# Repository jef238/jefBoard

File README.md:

# jefBoard

## Cos'è

JefBoard è una scheda di sviluppo basata sul microcontroller Attiny2313 della ATMEL. Si presta allo sviluppo di applicazioni di varia natura e integra la predisposizione per la scheda WiFI ESP-01 (Opzionale) e il connettore per la programmazione ISP dell'Attiny2313.
Alcune caratteristiche:
- JefBoard espone tutti i pin dell'Attiny2313 per il loro utilizzo.
- JefBoard permette la realizzazione di applicazioni con supporto WiFi (il modulo ESP-01 comunica tramite connessione seriale con l'Attiny2313).
- JefBoard può essere assemblata anche senza l'ESP-01 e relativi componenti di alimentazione se non si necessita di supporto WiFi abbassando ulteriormente il costo.
- JefBoard è una scheda di piccole dimensioni 6x4 cm.

## Attiny 2313 pinout

# Schema ed elenco componenti

# PCB Layout
Per reperire la PCB scrivi al mio indirizzo giuseppe.culotta@gmail.com

## Elenco componenti

| Sigla | Valore                        | Tipo			        | Note                                        |
|-------|-------------------------------|-------------------------------|---------------------------------------------|
| C1    | 100n           		| Condensatore poliestere        |				              |    
| C2    | 100u           		| Condensatore elettrolitico     |					      |
| C4    | 10u            		| Condensatore elettrolitico     | (Opzionale - Solo in caso di supporto WIFI) |	
| C5    | 22p            		| Condensatore ceramico          |					      |
| C6    | 22p            		| Condensatore ceramico          | 					      |
| ESP01 |                 		| Connettore pin		| (Opzionale - Solo in caso di supporto WIFI) |
| IC1   | ATtiny2313/ATtiny2313a        | AVR			        |				              |
| IC2   | LM1117DTX 3.3V 		|			        | (Opzionale - Solo in caso di supporto WIFI) |	
| JP1   |                  		| Connettore tipo M100.1	| (Opzionale)                  		      |
| JP2   |                  		| Connettore tipo M100.1	| (Opzionale)                                 |
| LED1  |                  		| LED3MM                        |				              |
| PWR   |                  		| Connettore tipo W237-102      | (Opzionale)                                 |
| Q1    |                   		| Quarzo 4MHZ    	        |	                                      |
| R1    | 10k            		| 1/4w		                |                                             |
| R2    | 1k            		| 1/4w 				| (Opzionale - Solo in caso di supporto WIFI) |	
| R3    | 2k            		| 1/4w 	        		| (Opzionale - Solo in caso di supporto WIFI) |	
| R4    | 220            		| 1/4w                		| 					      |
| RESET1|                  		| Microswitch                   |                                             |
| RESET2|                 		| Microswitch			| (Opzionale - Solo in caso di supporto WIFI) |
| SV2   |                   		| Connettore pin                |                                             |
         
# Programmazione

Io utilizzo Xcode e [CrossPack for AVR Development](https://github.com/obdev/CrossPack-AVR) in ambiente Mac.

In ambiente Windows vi consiglio di utilizzare Atmel Studio 7 ma sembra che recentemente sia stato sostituito da un altro prodotto: https://www.microchip.com/en-us/tools-resources/develop/microchip-studio.
Se utilizzate Atmel Studio ricordate di selezionare l'Attiny2313a come chip durante la creazione del progetto ed eseguire i seguenti step:
- Project->Properties->Toolchain->AVR/GNU C Compiler->Symbols: aggiungere F_CPU=2000000  (In questo caso la frequenza di clock è di 2MHZ)

- Impostare USBTINY come external tool (https://www.programming-electronics-diy.xyz/2020/09/using-usbtinyisp-programmer-with-atmel.html), in questo modo potete scrivere il firmware in formato hex sul chip direttamente dall'interfaccia di Atmel Studio dal menu Tools.

Come programmatore hardware per l'ISP ho utilizzato l'USBtinyISP:

## 1. Impostazione FUSE bits

Questa procedura deve essere eseguita solo una volta poichè serve a settare le impostazioni di base del bootloader del chip   

- Utilizzare AVR Calculator per ottenere la stringa corretta (http://www.engbedded.com/fusecalc)

    ESEMPI:
    ```
    /* Oscillatore interno 1MHZ */     						-U lfuse:w:0x64:m -U hfuse:w:0xdf:m -U efuse:w:0xff:m
    /* Quarzo esterno da 3 a 8MHZ */   						-U lfuse:w:0xfd:m -U hfuse:w:0xdf:m -U efuse:w:0xff:m
    /* Quarzo esterno da 16MHZ con CKDIV8 e frequenza effettiva 2MHZ */		-U lfuse:w:0x5e:m -U hfuse:w:0xdf:m -U efuse:w:0xff:m     
    ```
- Impostare i FUSE Bits nell'Attiny2313:
   ```
   avrdude -c usbtiny -p t2313 -e -U lfuse:w:0xfd:m -U hfuse:w:0xdf:m -U efuse:w:0xff:m
   ```

## 2a. Compilazione su Xcode (Mac)

- Modificare le righe seguenti nel file Makefile (ATTENZIONE: la riga FUSES deve essere identica alle impostazioni di FUSE Bits dell'Attiny2313; in questo esempio si utilizza un quarzo esterno da 4MHZ):
	```
	DEVICE     = attiny2313
	CLOCK      = 4000000
	PROGRAMMER = -c usbtiny -p attiny2313
	OBJECTS    = main.o
	FUSES      = -U lfuse:w:0xFD:m -U hfuse:w:0xDF:m -U efuse:w:0xFF:m -U lock:w:0xFF:m
  ```
- effettuare build (verrà generato main.hex)

## 2b. Compilazione su Atmel Studio (Windows)

- Menu Build->Build "nome progetto"
                                                             
## 3. Collegare l'USBtinyISP

- Assicurarsi di aver correttamente collegato il programmatore al computer e di aver installato i driver per il suo funzionamento (su Mac non è necessario installare driver)

- Collegare l'USBtinyISP al connettore SV2

## 4a. Flash su Mac

- Caricare il file .hex nel chip: 
   ```
   avrdude -c usbtiny -p t2313 -e -U flash:w:main.hex
   ```
## 4b. Flash su Windows (Atmel Studio)

- Menu Tools->USBTiny (per la configurazione vedi https://www.programming-electronics-diy.xyz/2020/09/using-usbtinyisp-programmer-with-atmel.html)

# Utilizzo dell'ESP01 per il supporto WIFI

L'ESP01 è un modulo SOC basato sul chip ESP8266 che permette di aggiungere il supporto al WIFI in modo semplice ed economico.
Prima di inserirlo sulla jefBoard è necessario fare una precisazione:
L'ESP01 viene fornito generalmente con un firmware dotato di soli comandi AT per cui prima di utilizzarlo nei nostri progetti è necessario caricare il firmware nodeMCU (https://it.wikipedia.org/wiki/NodeMCU). Con questo firmware è possibile programmare facilmente l'ESP01 tramite linguaggio LUA ed è possibile compilare una versione custom di nodeMCU con il supporto delle librerie/funzionalità necessarie in base all'utilizzo su https://nodemcu-build.com.

E' necessario inoltre dotarsi di un adattore USB seriale TTL:

## Istruzioni per l’installazione di esptool su MACOSX:

- Scaricare e scompattare esptool (https://github.com/espressif/esptool)

- Assicurarsi di avere Python 1.7 o successivo installato sul sistema

- Spostarsi sulla directory appena scompattata ed eseguire:
   ```
   sudo python setup.py install
   ```

## Istruzioni per flash nodemcu su ESP01
Esistono tanti modi per abilitare la modalità flash su ESP-01 (una ricerca su google è altamente consigliata...). Tempo fa ho realizzato una scheda che per comodità mi permette di riavviare tramite reset l'ESP01 (pulsante 1) mentre metto a massa il pin GPIO0 (pulsante 2):

- Posizionare l’ESP01 e l’interfaccia seriale/USB sulla scheda di programmazione:

- Per settare l’ESP01 in modalità flash tenere premuto il pulsante 2 e contemporaneamente effettuare un reset premendo e rilasciando il pulsante 1; dopo qualche istante rilasciare il pulsante 2.

- Effettuare il comando (nodemcu_base_int.bin è il nome del file del firmware nodemcu da flashare vedi cartella esp8266):
   ```  
   python esptool.py --port /dev/tty.wchusbserialfa140 write_flash 0x00000 nodemcu_base_int.bin
   ```
- (opzionale) restore firmware originale (11/12/2019)
   ``` 
   python esptool.py --port /dev/tty.wchusbserialfd130 write_flash 0x00000 v0.9.2.2\ AT\ Firmware.bin
   ``` 
## Programmazione ESP01 tramite script LUA
Una volta caricato il firmware nodeMCU è possibile caricare gli script LUA. Il file denominato init.lua viene caricato all'avvio in maniera automatica.
E' possibile utilizzare il software ESPlorer (https://github.com/4refr0nt/ESPlorer) sia per caricare sia gli script LUA che per gestire al meglio l'ESP01.

# Utilizzo di jefBoard come server WIFI
In questo caso l'ESP01 funge da server in ascolto sulla porta 8080 tramite connessione WIFI; Ricevuto il comando lo inoltra tramite la connessione seriale verso l'Attiny2313.
Per questo utilizzo è necessario che la scheda sia equipaggiata con l'ESP01 aggiornata con il firmware nodeMCU, ed i relativi componenti. Di seguito un esempio di file init.lua (da caricare sull'ESP01) e del codice da utilizzare sull'Attiny2313:

## init.lua (ESP01)

```
wifi.setmode(wifi.SOFTAP)
cfg={}
cfg.ssid="jefBoard"
wifi.ap.config(cfg)

uart.setup(0, 9600, 8, uart.PARITY_NONE, uart.STOPBITS_1, 1)

sv = net.createServer(net.TCP, 30)

function receiver(sck, data)
  print(data)  --senda data to jefBoard by serial
end

if sv then
  sv:listen(8080, function(conn)
    conn:on("receive", receiver)    
  end)
end
```

## main.c (jefBoard/Attiny2313)

```
#define F_CPU 4000000 UL // 4 MHz Crystal

#include <avr/io.h>
#include <util/delay.h>
#include <avr/interrupt.h>

// Define baud rate
#define USART_BAUDRATE 9600
#define BAUD_PRESCALE (((F_CPU / (USART_BAUDRATE * 16UL))) - 1)

volatile unsigned char value;
/* This variable is volatile so both main and RX interrupt can use it.
 It could also be a uint8_t type */

/* Interrupt Service Routine for Receive Complete
 NOTE: vector name changes with different AVRs see AVRStudio -
 Help - AVR-Libc reference - Library Reference - <avr/interrupt.h>: Interrupts
 for vector names other than USART_RX_vect for Attiny2313 */

void dosomething(); //Exec something

void USART_Init(void) {
  // Set baud rate
  UBRRL = BAUD_PRESCALE; // Load lower 8-bits into the low byte of the UBRR register
  UBRRH = (BAUD_PRESCALE >> 8);
  /* Load upper 8-bits into the high byte of the UBRR register
   Default frame format is 8 data bits, no parity, 1 stop bit
   to change use UCSRC, see AVR datasheet*/

  // Enable receiver and transmitter and receive complete interrupt
  UCSRB = ((1 << TXEN) | (1 << RXEN) | (1 << RXCIE));
}

void USART_SendByte(uint8_t u8Data) {

  // Wait until last byte has been transmitted
  while ((UCSRA & (1 << UDRE)) == 0);

  // Transmit data
  UDR = u8Data;
}

// not being used but here for completeness
// Wait until a byte has been received and return received data
uint8_t USART_ReceiveByte() {
  while ((UCSRA & (1 << RXC)) == 0);
  return UDR;
}

ISR(USART_RX_vect) {
  if (UDR != 0x0A) value = UDR; //read UART register into value except <RETURN> key
}

void dosomething() {
  //Exec something    
}

int main(void) {

  USART_Init(); // Initialise USART
  sei(); // enable all interrupts

  //If received data from serial match 'd' char exec dosomething() function
  while (1) {
    if (value == 0x64) dosomething(); //ASCII for 'd'     
  }

  return 0;
}
``` 
## Contatti

giuseppe.culotta@gmail.com

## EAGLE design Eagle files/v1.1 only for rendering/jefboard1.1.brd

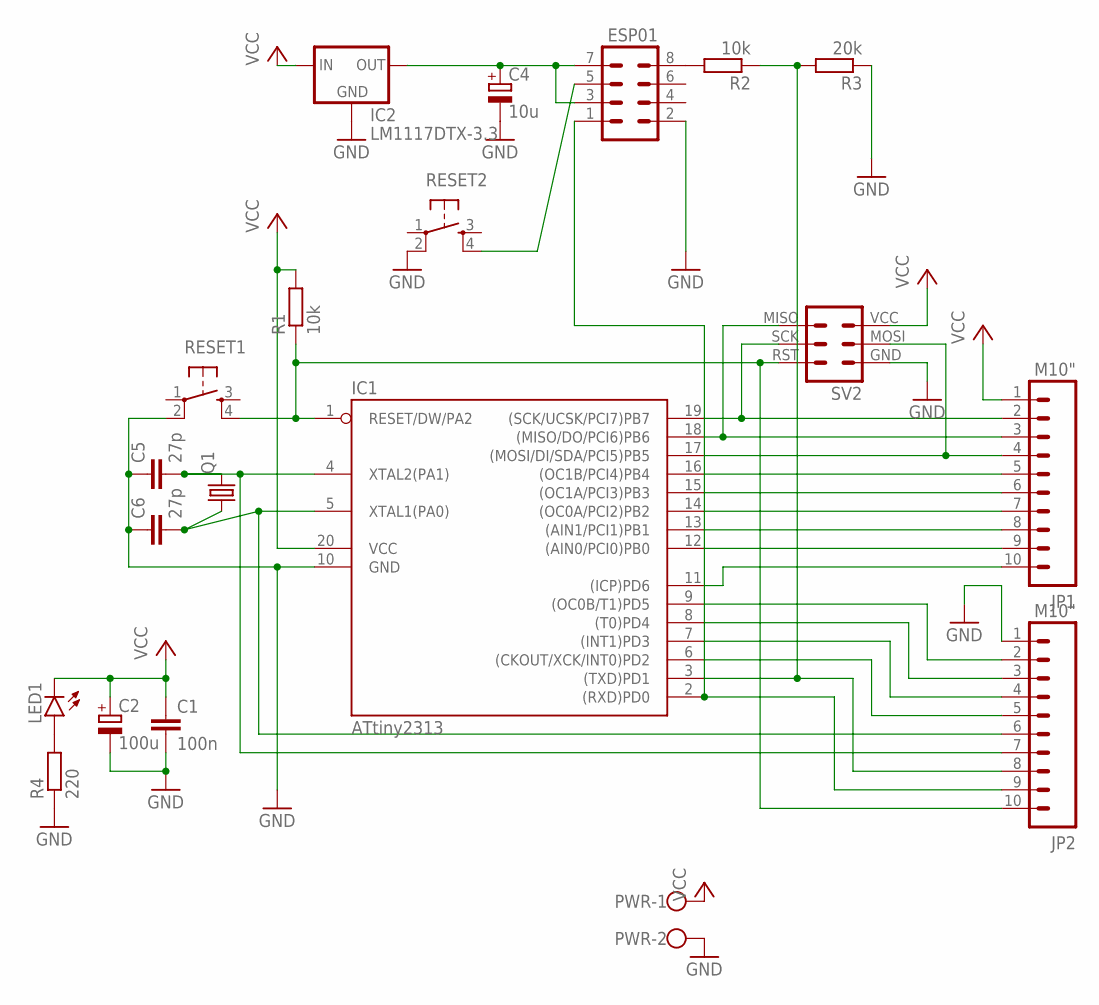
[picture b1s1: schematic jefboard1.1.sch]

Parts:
C1: 100n; C025-025X050
C2: 100u; E2,5-5
C4: 10u; E2,5-5
C5, C6: 27p; C2.5-2
ESP01: MA04-2
IC1: ATtiny2313; DIL20
IC2: LM1117DTX-3.3; TO252
JP1, JP2: M10"; 1X10
LED1: LED3MM
PWR: W237-102
Q1: CRYSTALHC49S; HC49/S
R1, R2: 10k; 0207/5V
R3: 20k; 0207/5V
R4: 220; 0207/5V
RESET1, RESET2: TAC_SWITCHPTH; TACTILE-PTH
SV2: MA03-2

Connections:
GND: C1.2, C2.-, C4.-, C5.1, C6.1, ESP01.2, IC1.10 (GND), IC2.1 (GND), JP2.1, PWR.2, R3.1, R4.1, RESET1.2, RESET2.2, SV2.GND
unnamed: C4.+, ESP01.3, ESP01.7, IC2.TAB (OUT)
unnamed: C5.2, IC1.4 (XTAL2(PA1)), JP2.7, Q1.2
unnamed: C6.2, IC1.5 (XTAL1(PA0)), JP2.6, Q1.1
unnamed: IC1.1 (RESET/DW/PA2), JP2.10, R1.1, RESET1.4, SV2.RST
unnamed: IC1.19 ((SCK/UCSK/PCI7)PB7), JP1.2, SV2.SCK
unnamed: IC1.18 ((MISO/DO/PCI6)PB6), JP1.3, SV2.MISO
unnamed: IC1.17 ((MOSI/DI/SDA/PCI5)PB5), JP1.4, SV2.MOSI
unnamed: IC1.16 ((OC1B/PCI4)PB4), JP1.5
unnamed: IC1.15 ((OC1A/PCI3)PB3), JP1.6
unnamed: IC1.14 ((OC0A/PCI2)PB2), JP1.7
unnamed: IC1.13 ((AIN1/PCI1)PB1), JP1.8
unnamed: IC1.12 ((AIN0/PCI0)PB0), JP1.9
unnamed: IC1.11 ((ICP)PD6), JP1.10
unnamed: IC1.9 ((OC0B/T1)PD5), JP2.2
unnamed: IC1.8 ((T0)PD4), JP2.3
unnamed: IC1.7 ((INT1)PD3), JP2.4
unnamed: IC1.6 ((CKOUT/XCK/INT0)PD2), JP2.5
unnamed: IC1.3 ((TXD)PD1), JP2.8, R2.1, R3.2
unnamed: ESP01.5, RESET2.4
unnamed: ESP01.8, R2.2
unnamed: LED1.A, R4.2
RX: ESP01.1, IC1.2 ((RXD)PD0), JP2.9
VCC: C1.1, C2.+, IC1.20 (VCC), IC2.2 (IN), JP1.1, LED1.K (C), PWR.1, R1.2, SV2.VCC

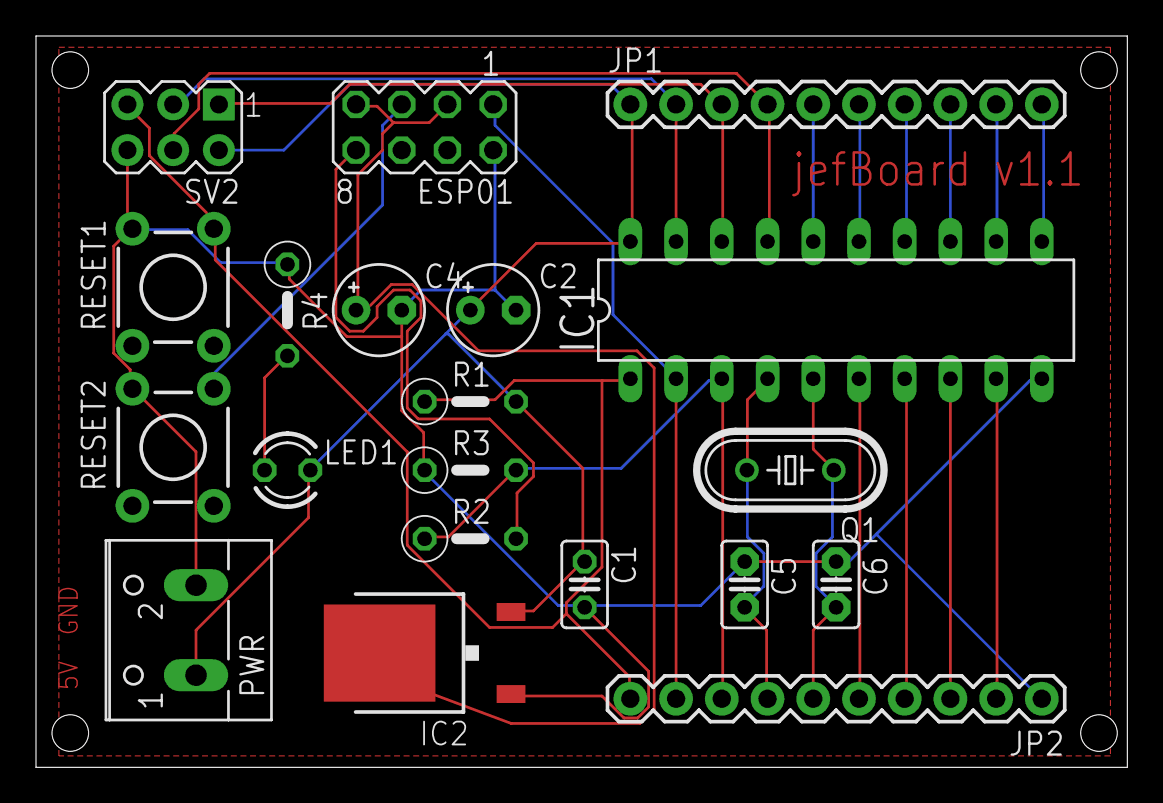
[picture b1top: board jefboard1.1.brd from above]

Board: 2 copper layers, 60.6 x 40.6 mm, 20 parts (0 on the bottom side), 24 nets.

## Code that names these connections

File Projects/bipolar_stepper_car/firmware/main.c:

/* Name: main.c
 * Author: <insert your name here>
 * Copyright: <insert your copyright message here>
 * License: <insert your license reference here>
 */

#include <avr/io.h>
#include <util/delay.h>

void myDelay();
void up();
void down();
void left();
void right();

int main(void)
{
    
    DDRB |= (1 << PB6) | (1 << PB5) | (1 << PB4) | (1 << PB3) | (1 << PB2) | (1 << PB1) | (1 << PB0); //Setup as output
    DDRD |= 1 << PD6; //Setup as output
    
    DDRD &= ~(1 << PD5); //Setup as input
    PORTD |= (1 << PD5); //Enable pullup resistor
    
    DDRD &= ~(1 << PD4); //Setup as input
    PORTD |= (1 << PD4); //Enable pullup resistor
    
    DDRD &= ~(1 << PD3); //Setup as input
    PORTD |= (1 << PD3); //Enable pullup resistor
    
    DDRD &= ~(1 << PD2); //Setup as input
    PORTD |= (1 << PD2); //Enable pullup resistor
    
#define Ax_on  PORTB |= (1 <<  PB2);
#define Bx_on  PORTB |= (1 <<  PB1);
#define Cx_on  PORTB |= (1 <<  PB0);
#define Dx_on  PORTD |= (1 <<  PD6);
#define Ax_off  PORTB &= ~(1 <<  PB2);
#define Bx_off  PORTB &= ~(1 <<  PB1);
#define Cx_off  PORTB &= ~(1 <<  PB0);
#define Dx_off  PORTD &= ~(1 <<  PD6);

#define Ay_on  PORTB |= (1 <<  PB6);
#define By_on  PORTB |= (1 <<  PB5);
#define Cy_on  PORTB |= (1 <<  PB4);
#define Dy_on  PORTB |= (1 <<  PB3);
#define Ay_off  PORTB &= ~(1 <<  PB6);
#define By_off  PORTB &= ~(1 <<  PB5);
#define Cy_off  PORTB &= ~(1 <<  PB4);
#define Dy_off  PORTB &= ~(1 <<  PB3);
    
    while(1){
        if ((PIND & (1 << PD5)) == 0) {    // is switch closed?
            up();
        }
        if ((PIND & (1 << PD4)) == 0) {    // is switch closed?
            down();
        }
        if ((PIND & (1 << PD3)) == 0) {    // is switch closed?
            left();
        }
        if ((PIND & (1 << PD2)) == 0) {    // is switch closed?
            right();
        }
        //else reset..
        Ax_off;
        Ay_off;
        Bx_off;
        By_off;
        Cx_off;
        Cy_off;
        Dx_off;
        Dy_off;
    }
    
    return 0;
}

void myDelay(){
    _delay_ms(5);
}

void up(){
    Ax_on;
    Ay_on;
    myDelay();
    Ax_off;
    Ay_off;
    Bx_on;
    By_on;
    myDelay();
    Bx_off;
    By_off;
    Cx_on;
    Cy_on;
    myDelay();
    Cx_off;
    Cy_off;
    Dx_on;
    Dy_on;
    myDelay();
    Dx_off;
    Dy_off;
}

void down(){
    Dx_on;
    Dy_on;
    myDelay();
    Dx_off;
    Dy_off;
    Cx_on;
    Cy_on;
    myDelay();
    Cx_off;
    Cy_off;
    Bx_on;
    By_on;
    myDelay();
    Bx_off;
    By_off;
    Ax_on;
    Ay_on;
    myDelay();
    Ax_off;
    Ay_off;
}

void right(){
    Ax_on;
    Dy_on;
    myDelay();
    Ax_off;
    Dy_off;
    Bx_on;
    Cy_on;
    myDelay();
    Bx_off;
    Cy_off;
    Cx_on;
    By_on;
    myDelay();
    Cx_off;
    By_off;
    Dx_on;
    Ay_on;
    myDelay();
    Dx_off;
    Ay_off;
}

void left(){
    Dx_on;
    Ay_on;
    myDelay();
    Dx_off;
    Ay_off;
    Cx_on;
    By_on;
    myDelay();
    Cx_off;
    By_off;
    Bx_on;
    Cy_on;
    myDelay();
    Bx_off;
    Cy_off;
    Ax_on;
    Dy_on;
    myDelay();
    Ax_off;
    Dy_off;
}

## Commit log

2025-11-18 Update resistor values for WIFI support
2025-11-18 Remove PCB image from README
    Removed the PCB image from the README.
